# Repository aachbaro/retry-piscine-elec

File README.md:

## (BOM)

| Réf    | Composant                         | Valeur / Type              | Boîtier      |
| ------ | --------------------------------- | -------------------------- | ------------ |
| U1     | ATmega328P-AU                     | Microcontrôleur AVR 20 MHz | TQFP-32      |
| Y1     | Quartz 16 MHz                     | 9 pF                       | SMD 3225     |
| C1, C2 | Condensateurs charge quartz       | 12 pF C0G                  | 0603         |
| C3–C8  | Condensateurs découplage          | 100 nF X7R                 | 0603         |
| C9     | Condensateur découplage principal | 1 µF X5R                   | 0603         |
| R1     | Résistance LED                    | 330 Ω                      | 0603         |
| R2     | Résistance pull-up / pull-down    | 10 kΩ                      | 0603         |
| D1     | LED                               |                            | 0603         |
| SW1    | Bouton poussoir SMD               | 3×2.5 mm                   | SMD          |
| J1     | Header programmation ISP          | 2.54 mm                    | Through-hole |
| J2     | Header alimentation               | 2.54 mm                    | Through-hole |

## 🧷 Pinout

| Pin | Nom  | Fonction      |
| --- | ---- | ------------- |
| 1   | PD3  | D3 / INT1     |
| 2   | PD4  | D4            |
| 3   | GND  | Masse         |
| 4   | VCC  | Alim 5V       |
| 5   | GND  | Masse         |
| 6   | VCC  | Alim 5V       |
| 7   | PB6  | XTAL1         |
| 8   | PB7  | XTAL2         |
| 9   | PD5  | D5 / PWM      |
| 10  | PD6  | D6 / PWM      |
| 11  | PD7  | D7            |
| 12  | PB0  | D8            |
| 13  | PB1  | D9 / PWM      |
| 14  | PB2  | D10 / SS      |
| 15  | PB3  | D11 / MOSI    |
| 16  | PB4  | D12 / MISO    |
| 17  | PB5  | D13 / SCK     |
| 18  | AVCC | Alim ADC      |
| 19  | ADC6 | A6            |
| 20  | AREF | Référence ADC |
| 21  | GND  | Masse         |
| 22  | ADC7 | A7            |
| 23  | PC0  | A0            |
| 24  | PC1  | A1            |
| 25  | PC2  | A2            |
| 26  | PC3  | A3            |
| 27  | PC4  | A4 / SDA      |
| 28  | PC5  | A5 / SCL      |
| 29  | PD0  | RX            |
| 30  | PD1  | TX            |
| 31  | PD2  | D2 / INT0     |
| 32  | PD3  | D3            |

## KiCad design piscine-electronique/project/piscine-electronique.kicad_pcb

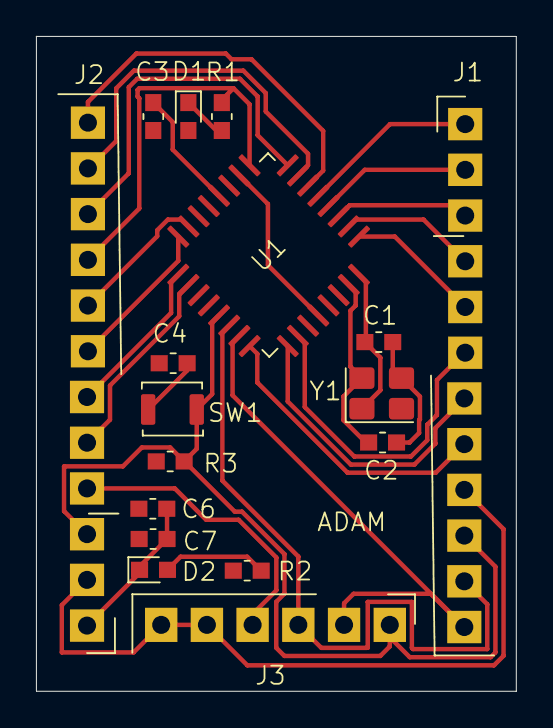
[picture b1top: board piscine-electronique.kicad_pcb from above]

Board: 2 copper layers, 26.7 x 36.4 mm, 17 parts (0 on the bottom side), 30 nets.

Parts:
C1, C2: 12pF; C_0603
C3, C4, C7: 100nF; C_0603
C6: 1uF; C_0603
D1: Green; LED_0603
D2: RED; LED_0603
J1, J2: PinHeader_1x12
J3: FTDI; PinHeader_1x06
R1: 330; R_0603
R2, R3: 10K; R_0603
SW1: SW_Push; SW_Push_B3U
U1: ATmega328P-A; TQFP-32_7x7
Y1: 16MHz; crystal_SMD

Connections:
A0: J2.8, U1.23 (PC0)
A1: J2.7, U1.24 (PC1)
A2: J2.6, U1.25 (PC2)
A3: J2.5, U1.26 (PC3)
D2: J1.8, U1.32 (PD2)
D3: J1.7, U1.1 (PD3)
D4: J1.6, U1.2 (PD4)
D5: J1.5, U1.9 (PD5)
D6: J1.4, U1.10 (PD6)
D7: J1.3, U1.11 (PD7)
D8: J1.2, U1.12 (PB0)
D9: J1.1, U1.13 (PB1)
D10: J2.12, U1.14 (PB2)
DTR: J1.10, J2.3, J3.1, R3.2, SW1.2, U1.29 (RESET/PC6)
GND: J1.9, J2.2, J3.5, J3.6
MISO: J2.10, U1.16 (PB4)
MOSI: J2.11, U1.15 (PB3)
unnamed: C1.1, C2.2, Y1.2
unnamed: C4.2, SW1.1
unnamed: D1.1 (A), R1.2
unnamed: D2.2 (K), R2.1
unnamed: C3.2, U1.20 (AREF)
unnamed: U1.4 (VCC), U1.18 (AVCC)
unnamed: C2.1, U1.7 (XTAL1/PB6), Y1.1
unnamed: C1.2, U1.8 (XTAL2/PB7), Y1.3
RAW: C6.1, C7.1, D2.1 (A), J2.1
RXI: J1.11, J3.3, U1.30 (PD0)
SCK: J2.9, R1.1, U1.17 (PB5)
TXO: J1.12, J3.2, U1.31 (PD1)
VCC: J2.4, J3.4

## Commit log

2025-11-24 test 1
2025-11-26 v final
